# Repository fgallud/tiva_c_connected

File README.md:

# tiva_c_connected_tcp_modbus
It is a very simple tcp modbus example for the tiva c connected board. It is written in C for the Energia IDE

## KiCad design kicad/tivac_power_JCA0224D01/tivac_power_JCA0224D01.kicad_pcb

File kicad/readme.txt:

Some daughter boards for the tiva c ARM board

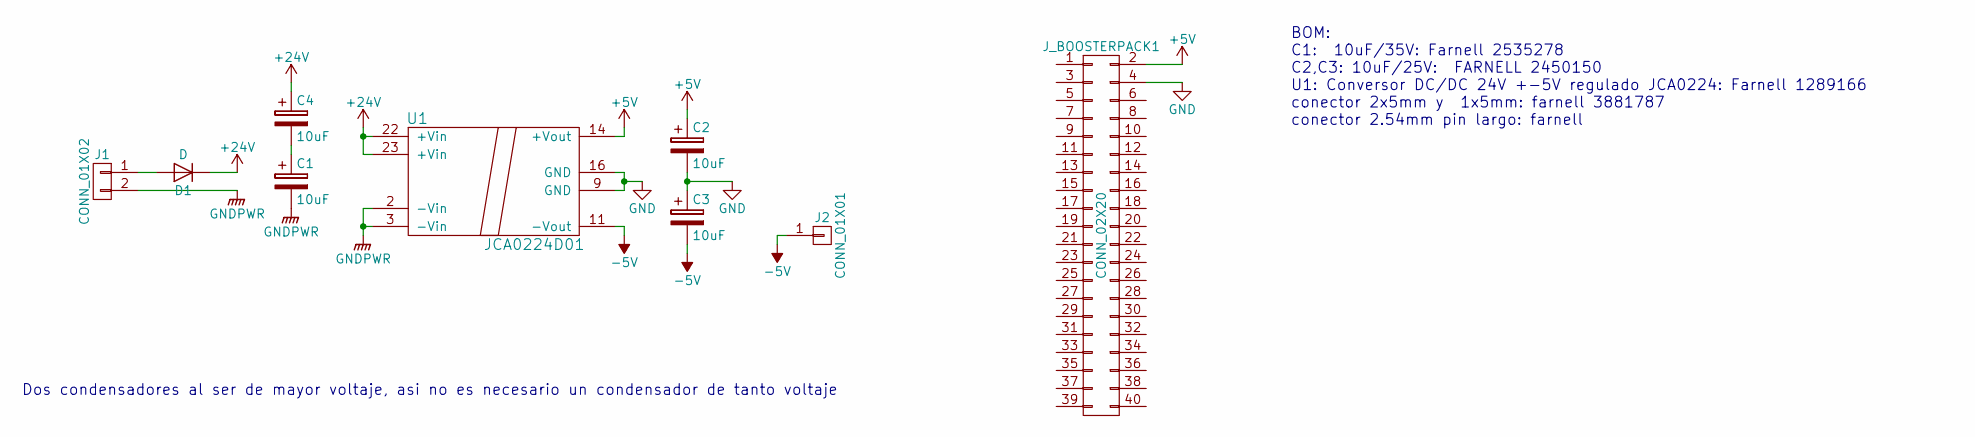
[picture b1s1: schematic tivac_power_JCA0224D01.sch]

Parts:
C1, C2, C3, C4: 10uF; CP_Tantalum_Case-C_EIA-6032-28_Hand
D1: D; D_MiniMELF_Handsoldering
J1: CONN_01X02; Header_2x1_pitch_5.0mm
J2: CONN_01X01; Header_1x1_pitch_5.0mm
J_BOOSTERPACK1: CONN_02X20; TIVA_BOOSTERPACK
U1: JCA0224D01; farnell 1289166

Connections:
+5V: C2.1, J_BOOSTERPACK1.2, U1.14 (+Vout)
+24V: C4.1, D1.1 (K), U1.22 (+Vin), U1.23 (+Vin)
-5V: C3.2, J2.1, U1.11 (-Vout)
GND: C2.2, C3.1, J_BOOSTERPACK1.4, U1.9 (GND), U1.16 (GND)
GNDPWR: C1.2, J1.2, U1.2 (-Vin), U1.3 (-Vin)
unnamed: C1.1, C4.2
unnamed: D1.2 (A), J1.1

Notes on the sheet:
BOM: C1: 10uF/35V: Farnell 2535278 C2,C3: 10uF/25V: FARNELL 2450150 U1: Conversor DC/DC 24V +-5V regulado JCA0224: Farnell 1289166 conector 2x5mm y 1x5mm: farnell 3881787 conector 2.54mm pin largo: farnell
Dos condensadores al ser de mayor voltaje, asi no es necesario un condensador de tanto voltaje

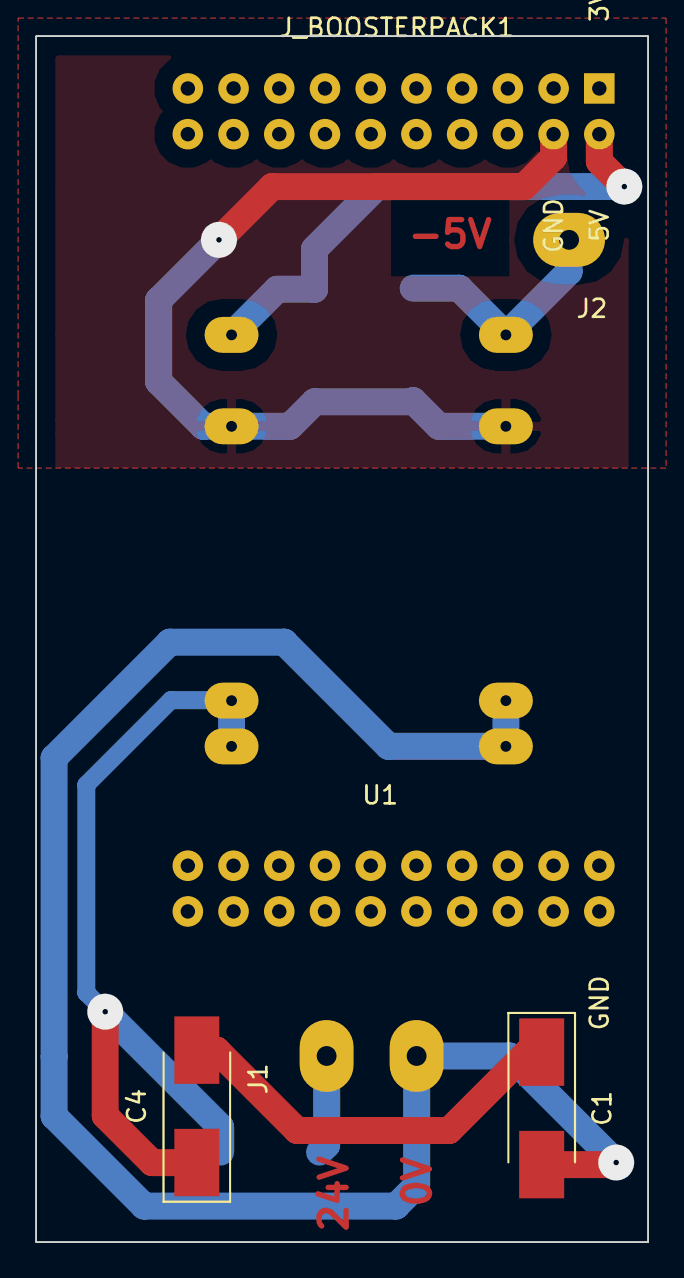
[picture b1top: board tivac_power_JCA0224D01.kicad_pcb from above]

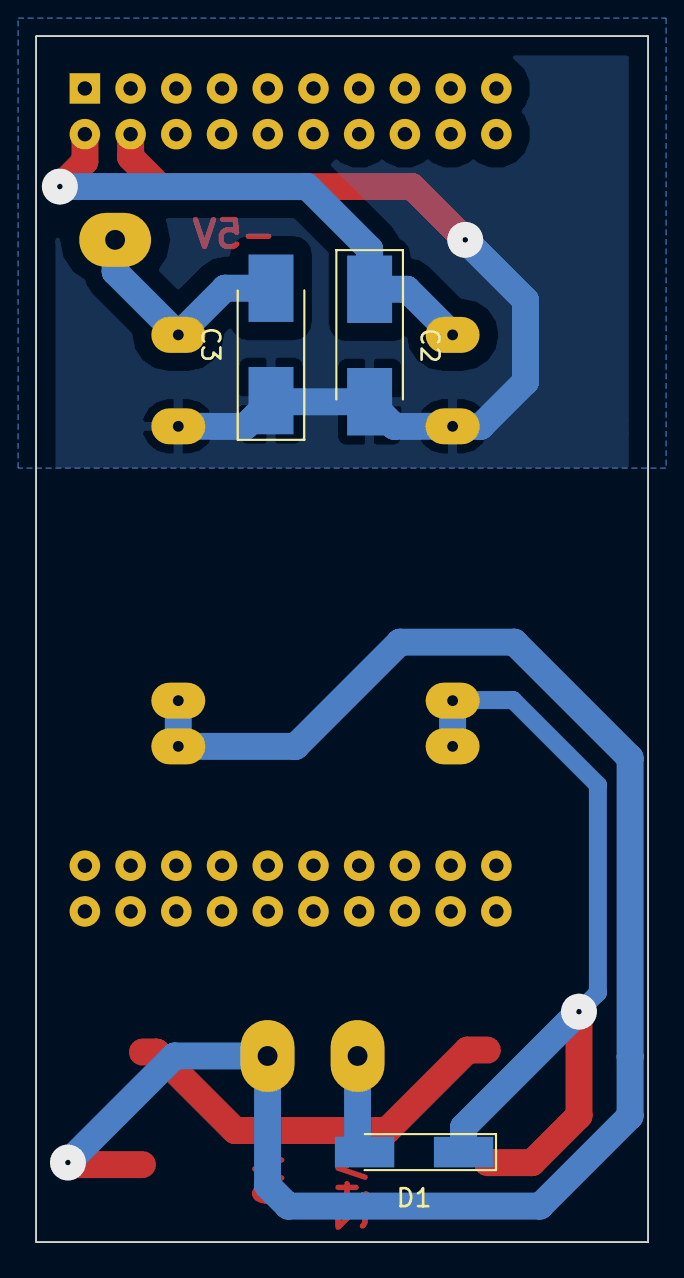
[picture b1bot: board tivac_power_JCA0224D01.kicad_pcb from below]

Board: 2 copper layers, 34.0 x 67.0 mm, 9 parts (3 on the bottom side), 7 nets.

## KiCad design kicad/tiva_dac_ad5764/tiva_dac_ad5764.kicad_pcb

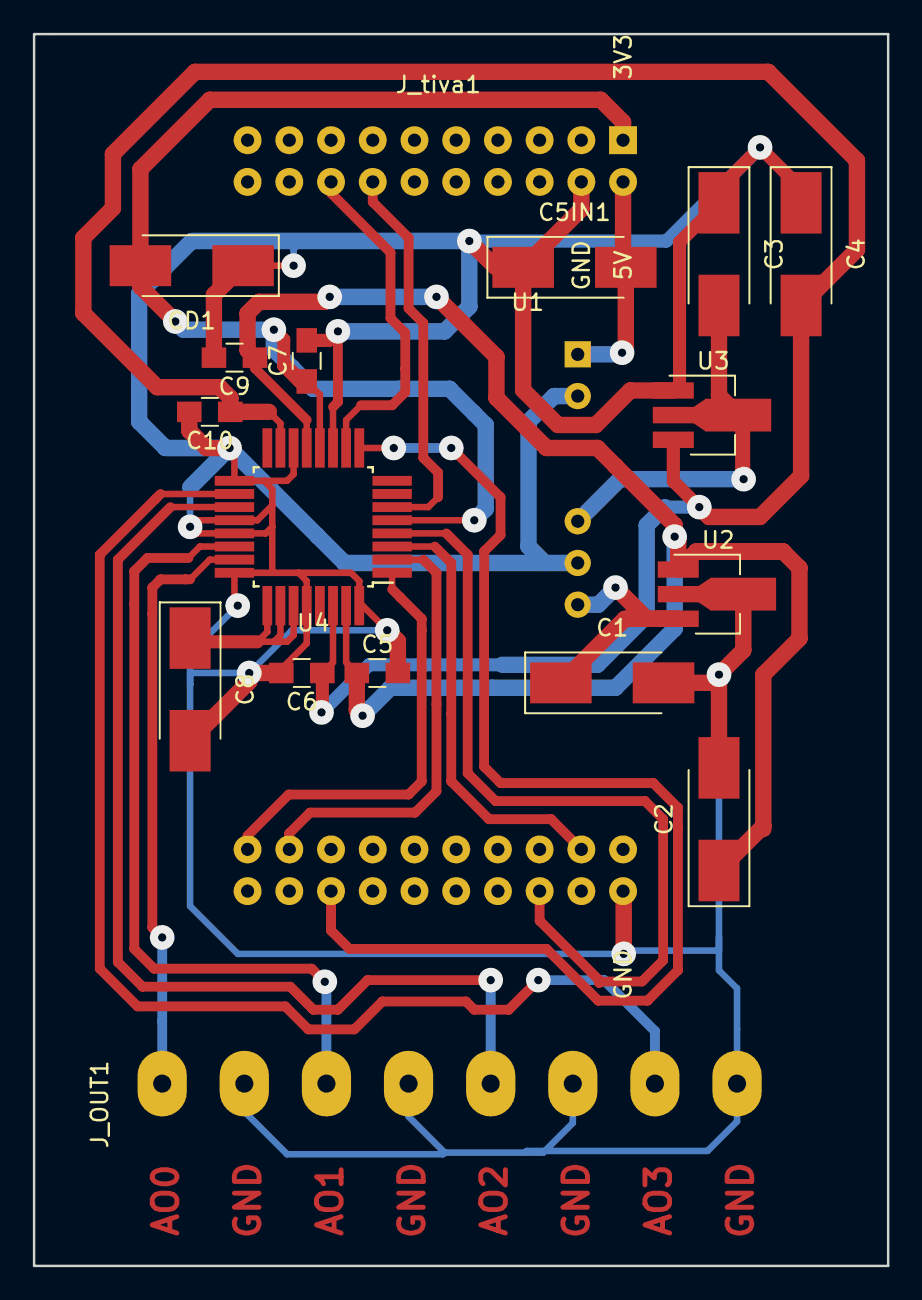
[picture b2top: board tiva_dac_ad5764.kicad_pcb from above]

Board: 2 copper layers, 52.0 x 75.0 mm, 18 parts (0 on the bottom side), 19 nets.

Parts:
C1, C2, C3, C4, C5IN1: 1uF; CP_Tantalum_Case-C_EIA-6032-28_Hand
C5, C6, C7, C9, C10: 100nF; C_0805_HandSoldering
C8: 10uF; CP_Tantalum_Case-C_EIA-6032-28_Hand
CD1: 1uF; CP_Tantalum_Case-C_EIA-6032-28_Hand
J_OUT1: CONN_01X08; Header_1x8_pitch_5.0mm
J_tiva1: CONN_02X20; TIVA_BOOSTERPACK
U1: CMR0515S3C
U2: L78L12; SOT89-3_Housing_Handsoldering
U3: L79L12; SOT89-3_Housing_Handsoldering
U4: AD5764; TQFP-32_HAND

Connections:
+3V3: C7.1, CD1.2, J_tiva1.1, U4.5, U4.12
+5V: C5IN1.2, J_tiva1.2, U1.1
+12V: C2.1, C5.1, C9.1, U2.1, U4.13, U4.31
-12V: C4.2, C6.1, C10.1, U3.3, U4.15, U4.30
/AO0: J_OUT1.1, U4.23
/AO1: J_OUT1.3, U4.22
/AO2: J_OUT1.5, U4.19
/AO3: J_OUT1.7, U4.18
/PK2: J_tiva1.14, U4.6
/PK3: J_tiva1.16, U4.10
/PK4: J_tiva1.23, U4.3
/PK6: J_tiva1.37, U4.2
/PK7: J_tiva1.39, U4.1
/PP3: J_tiva1.36, U4.9
/PP5: J_tiva1.26, U4.4
GND: C1.2, C2.2, C3.1, C4.1, C5.2, C5IN1.1, C6.2, C7.2, C8.2, C9.2, C10.2, CD1.1, J_OUT1.2, J_OUT1.4, J_OUT1.6, J_OUT1.8, J_tiva1.4, J_tiva1.22, U1.2, U1.6, U2.2, U3.1, U4.11, U4.14, U4.17, U4.20, U4.21, U4.24, U4.28, U4.32
unnamed: C1.1, U1.7, U2.3
unnamed: C3.2, U1.5, U3.2
unnamed: C8.1, U4.25, U4.26, U4.27

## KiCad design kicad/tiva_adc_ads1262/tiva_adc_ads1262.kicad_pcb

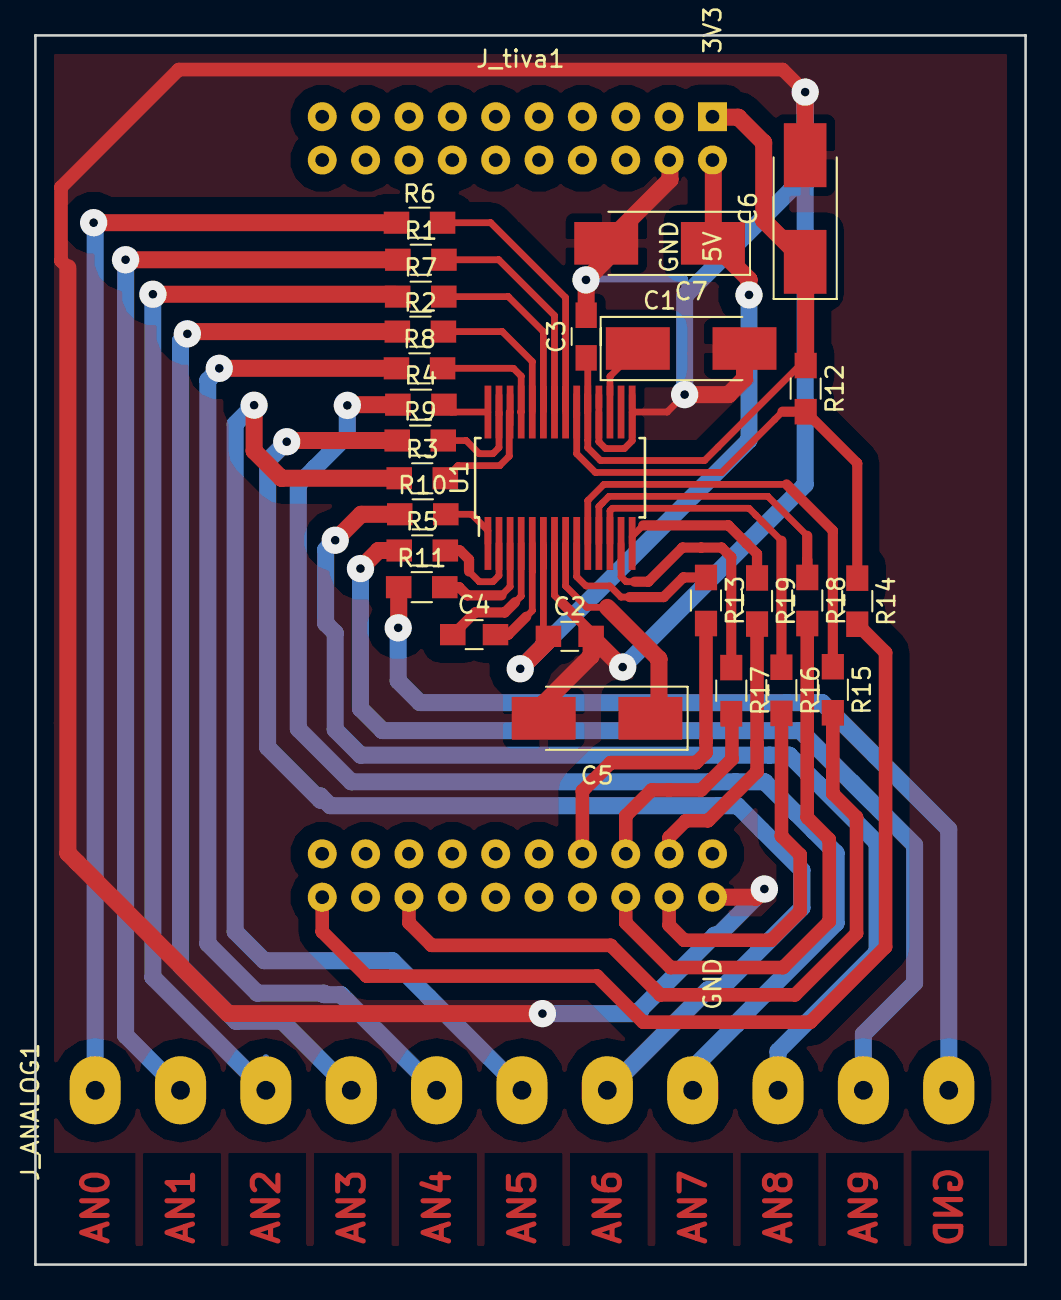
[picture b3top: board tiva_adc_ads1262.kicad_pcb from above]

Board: 2 copper layers, 58.0 x 72.0 mm, 29 parts (0 on the bottom side), 43 nets.

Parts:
C1, C6: 10uF; CP_Tantalum_Case-C_EIA-6032-28_Hand
C2, C3: 100nF; C_0805_HandSoldering
C4: 4.7nF; C_0805_HandSoldering
C5, C7: 1uF; CP_Tantalum_Case-C_EIA-6032-28_Hand
J_ANALOG1: CONN_01X11; Header_1x11_pitch_5.0mm
J_tiva1: CONN_02X20; TIVA_BOOSTERPACK
R1, R2, R3, R4, R5, R6, R7, R8, R9, R10, R11, R12: 10k; R_0805_HandSoldering
R13, R14, R15, R16, R17, R18, R19: 47; R_0805_HandSoldering
U1: ADS1262; TSSOP-28

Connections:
+3V3: C3.1, C6.1, J_tiva1.1, R12.1, U1.19
+5V: C1.1, C2.1, J_tiva1.2, U1.6
/AIN0: J_ANALOG1.1, R6.1
/AIN1: J_ANALOG1.2, R1.1
/AIN2: J_ANALOG1.3, R7.1
/AIN3: J_ANALOG1.4, R2.1
/AIN4: J_ANALOG1.5, R8.1
/AIN5: J_ANALOG1.6, R3.1
/AIN6: J_ANALOG1.7, R9.1
/AIN7: J_ANALOG1.8, R4.1
/AIN8: J_ANALOG1.9, R10.1
/AIN9: J_ANALOG1.10, R5.1
/AIN_GND: J_ANALOG1.11, R11.1
/PK4: J_tiva1.23, R19.2
/PK5: J_tiva1.25, R17.2
/PM0: J_tiva1.27, R13.2
/PM6: J_tiva1.40, R14.2
/PM7: J_tiva1.24, R16.2
/PP3: J_tiva1.36, R15.2
/PP5: J_tiva1.26, R18.2
GND: C1.2, C2.2, C3.2, C5.2, C6.2, C7.2, J_tiva1.4, J_tiva1.22, U1.7, U1.15, U1.18
unnamed: C4.1, U1.4
unnamed: C4.2, U1.5
unnamed: C5.1, U1.8
unnamed: C7.1, U1.17
unnamed: R1.2, U1.22
unnamed: R2.2, U1.24
unnamed: R3.2, U1.26
unnamed: R4.2, U1.28
unnamed: R5.2, U1.2
unnamed: R6.2, U1.21
unnamed: R7.2, U1.23
unnamed: R8.2, U1.25
unnamed: R9.2, U1.27
unnamed: R10.2, U1.1
unnamed: R11.2, U1.3
unnamed: R12.2, R14.1, U1.20
unnamed: R13.1, U1.9
unnamed: R15.1, U1.10
unnamed: R16.1, U1.12
unnamed: R17.1, U1.13
unnamed: R18.1, U1.11
unnamed: R19.1, U1.14
